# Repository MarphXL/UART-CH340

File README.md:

# CH340C
## Inhaltsverzeichnis
1. [x] [Inhaltsverzeichnis](#Inhaltsverzeichnis)
1. [X] [Beschreibung](#Beschreibung)
   1. [X] [Leitungen](#Leitungen)
1. [ ] [Hardware](#Hardware)
   1. [X] [Technische Daten](#technische-daten)
   1. [X] [Datasheet](#datasheet)
   1. [ ] [PCB](#PCB)
1. [ ] [Software](#Software)
1. [ ] [3D](#3D)
1. [X] [Where to buy](#Where-to-buy)
1. [X] [Abbildungen](#Abbildungen)
1. [x] [Credits](#Credits)

## Beschreibung
IC zur Umwandlung von seriellen Signalen zu USB. 
* Kompatibel mit 5V- und 3,3V-Systemen. 
* 2.0 Full-speed device
* Geschwindigkeit 50bps .. 2Mbps
* integrierter 12MHz crystal, kein externer benötigt
* USB-Vendor-class

* [Infoseite des Herstellers](http://www.wch-ic.com/products/CH340.html)
* [Downloadseite des Herstellers](http://www.wch-ic.com/search?q=CH340&t=downloads)

### Leitungen
###### Standard für Arduinos
PIN | Name | Beschreibung | TYP
------------ | ------------- | ------------- | -------------
RX | Receive Data | Leitung für eingehende (von DTE zu empfangende) Daten (negative Logik) | I
TX | Transmit Data | Leitung für ausgehende (von DTE gesendete) Daten ([negative Logik](https://de.wikipedia.org/wiki/Negative_Logik)) | O
DTR | Data Terminal Ready | Mit einem High-Pegel an diesem Ausgang signalisiert DTE seine Betriebsbereitschaft an die Gegenstelle. Damit kann die Gegenstelle, z. B. ein Modem, aktiviert oder auch zurückgesetzt werden. Üblicherweise antwortet die Gegenstelle mit einem High-Pegel auf DSR | O

###### Weitere für RS-232
PIN | Name | Beschreibung | TYP
------------ | ------------- | ------------- | -------------
CTS | Clear to Send | Hardware-Handshake, „Sendeerlaubnis“; Ein High-Pegel an diesem Eingang ist ein Signal der Gegenstelle, dass sie Daten von DTE entgegennehmen kann | I
RTS | Request to Send | Hardware-Handshake, „Sendeanforderung“; ein High-Pegel an diesem Ausgang signalisiert, dass DTE Daten senden möchte | O
RTR (n.v.) | Request to Receive | „Empfangsstatus“; ein High-Pegel an diesem Ausgang signalisiert der Gegenstelle, dass DTE bereit ist, Daten zu empfangen | O
DSR | Data Set Ready | Ein High-Pegel an diesem Eingang ist ein Signal der Gegenstelle, dass sie im Prinzip einsatzbereit ist (aber nicht notwendigerweise auch empfangsbereit, siehe CTS) | I
RI | Ring Indicator | Ein High-Pegel an diesem Eingang signalisiert dem DTE-Gerät, dass ein Anruf ankommt, d. h., dass jemand eine Datenverbindung aufbauen will („ring“ ist engl. für „klingeln“; besonders bei Telefonen und im übertragenen Sinne auch bei Modems). Siehe auch [Rufspannung](https://de.wikipedia.org/wiki/Rufspannung). | I
DCD | Data Carrier Detected | Mit einem High-Pegel an diesem Eingang signalisiert die Gegenstelle, dass sie einlaufende Daten auf der Leitung erkennt (dem Namen nach ist das die [Modulationsträger](https://de.wikipedia.org/wiki/Tr%C3%A4ger_(Nachrichtentechnik)-Erkennung) und an DTE weitergeben möchte | I

## Hardware
### Technische Daten
* Modell: Transceiver USB 2.0 2Mbps
* Typ: WCN CH340C
* Temperaturbereich: ?
* Versorgungsspannung: 3.3 V, 5 V
* LCSC Part #: [C84681](https://lcsc.com/product-detail/USB_CH340C_C84681.html/?href=jlc-SMT)
* EAN / GTIN: ?

### Datasheet
* [TI.com datasheet](https://www.ti.com/lit/ds/symlink/cd74hc4067.pdf)
* 04.11.2008 [snapshot Version 1D](datasheet/CH340_version_1D.PDF)
* unknown [snapshot Version 2C](datasheet/CH340_version_2C.PDF)
* 11.03.2019 chinese [snapshot Version 2G](datasheet/Jiangsu-Qin-Heng-CH340C_C84681.pdf)
### PCB
[SparkFun Serial Basic Breakout - CH340C and USB-C](https://github.com/sparkfun/Serial_Basic_Breakout-CH340C) released under the Creative Commons Attribution Share-Alike 4.0 license; designed by [N. Seidle](https://github.com/nseidle) @nseidle
## Software
## 3D

## Where to buy
~ 4 EUR for 10pcs: [AliExpress](https://www.aliexpress.com/wholesale?trafficChannel=main&d=y&CatId=0&SearchText=10pcs+ch340c&ltype=wholesale&SortType=default&maxPrice=2.6&page=1)
[SparkFun Serial Basic Breakout - CH340C and USB-C](https://www.sparkfun.com/products/15096)

## Abbildungen

## Credits
* :+1: [arduino](https://github.com/arduino)
* :+1: [adafruit](https://github.com/adafruit)
* :+1: [sparkfun](https://github.com/sparkfun)
* :+1: [Watterott](https://github.com/watterott) and @awatterott for great SW, HW and products
* :+1: [atom](https://github.com/atom) 
* :+1: @ikatyang for the [emoji-cheat-sheet](https://github.com/ikatyang/emoji-cheat-sheet/blob/master/README.md)

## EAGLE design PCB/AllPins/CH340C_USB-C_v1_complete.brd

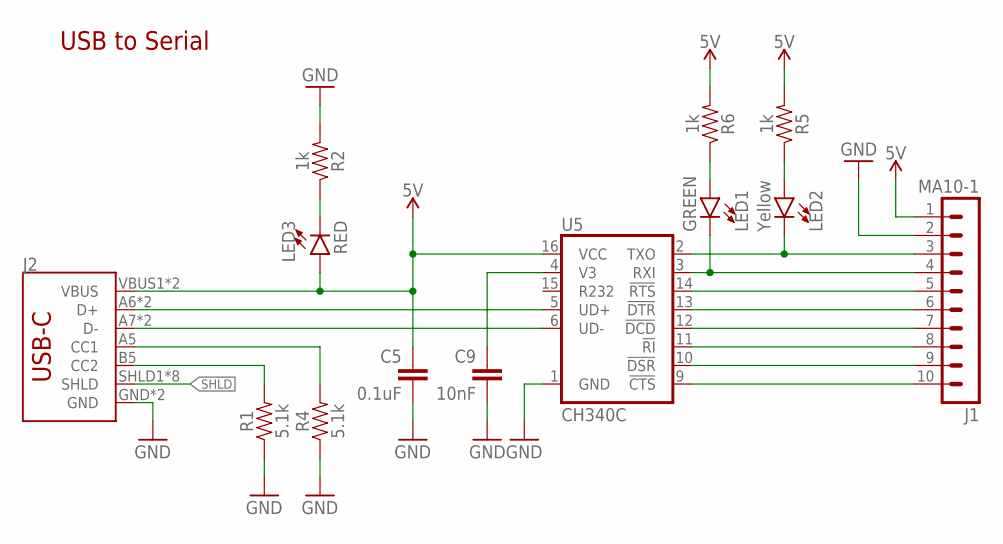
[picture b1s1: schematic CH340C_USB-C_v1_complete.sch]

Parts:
C5: 0.1uF; 0603
C9: 10nF; 0603
J1: MA10-1
J2: USB_C16PIN; USB-C-16P
LED1: GREEN; LED-0603
LED2: Yellow; LED-0603
LED3: RED; LED-0603
R1, R4: 5.1k; 0603
R2, R5, R6: 1k; 0603
U5: CH340C; SO016

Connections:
5V: C5.1, J1.1, J2.VBUS1 (VBUS), J2.VBUS2 (VBUS), LED3.A, R5.2, R6.2, U5.16 (VCC)
!CTS: J1.10, U5.9 (!CTS)
!DCD: J1.7, U5.12 (!DCD)
!DSR: J1.9, U5.10 (!DSR)
!DTR: J1.6, U5.13 (!DTR)
!RI: J1.8, U5.11 (!RI)
!RTS: J1.5, U5.14 (!RTS)
CC1: J2.A5 (CC1), R4.2
CC2: J2.B5 (CC2), R1.2
D+: J2.A6 (D+), J2.B6 (D+), U5.5 (UD+)
D-: J2.A7 (D-), J2.B7 (D-), U5.6 (UD-)
GND: C5.2, C9.2, J1.2, J2.GND, J2.GND2 (GND), R1.1, R2.2, R4.1, U5.1 (GND)
unnamed: LED3.C, R2.1
unnamed: LED1.A, R6.1
unnamed: LED2.A, R5.1
RXI: J1.4, LED1.C, U5.3 (RXI)
SHLD: J2.SHLD1 (SHLD), J2.SHLD2 (SHLD), J2.SHLD3 (SHLD), J2.SHLD4 (SHLD), J2.SHLD5 (SHLD), J2.SHLD6 (SHLD), J2.SHLD7 (SHLD), J2.SHLD8 (SHLD)
TXO: J1.3, LED2.C, U5.2 (TXO)
V3: C9.1, U5.4 (V3)

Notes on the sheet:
USB to Serial

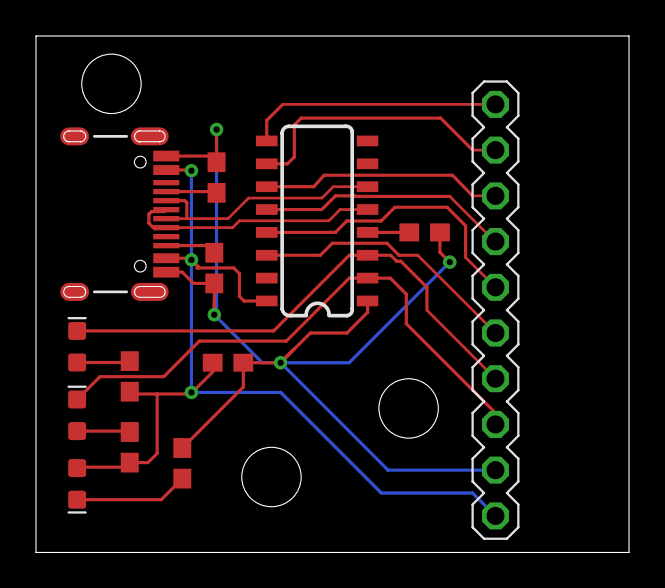
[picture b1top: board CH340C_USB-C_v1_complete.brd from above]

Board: 2 copper layers, 32.9 x 28.7 mm, 13 parts (0 on the bottom side), 19 nets.

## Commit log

2020-09-15 Create bla

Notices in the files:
parts and their libraries:
SparkFun-Capacitors: Licensing: Creative Commons ShareAlike 4.0 International - https://creativecommons.org/licenses/by-sa/4.0
